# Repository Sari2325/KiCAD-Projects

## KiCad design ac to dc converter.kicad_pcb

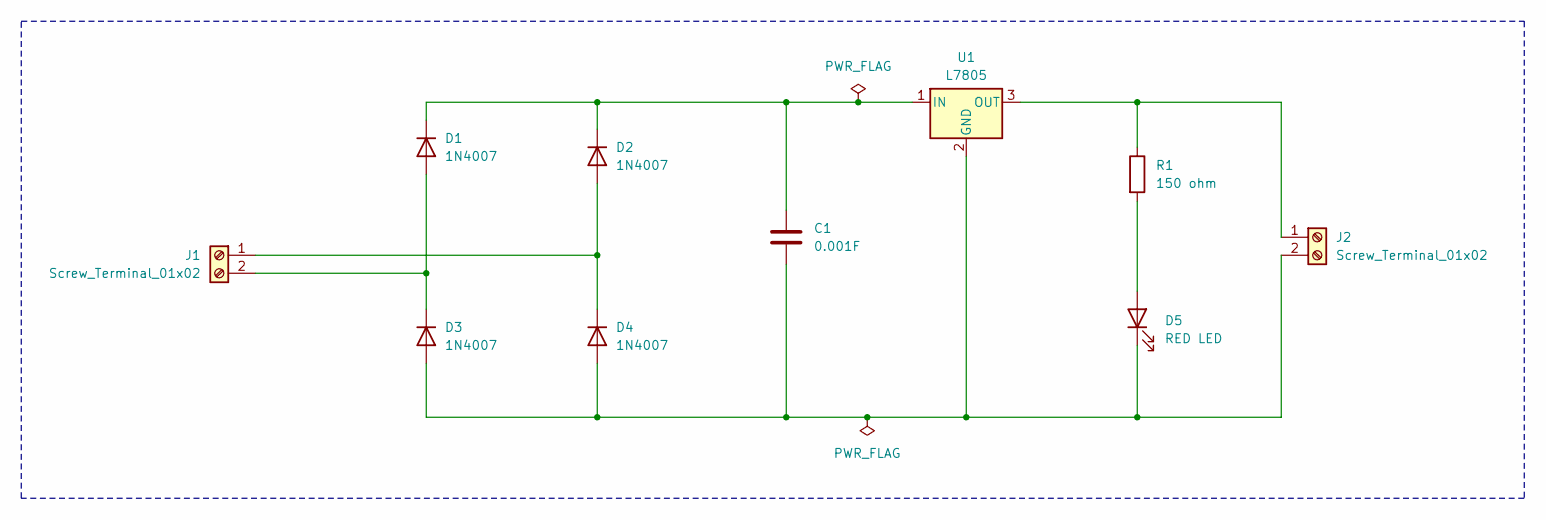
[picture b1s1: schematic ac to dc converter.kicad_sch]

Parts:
C1: 0.001F; C_Radial_D10.0mm_H16.0mm_P5.00mm
D1, D2, D3, D4: 1N4007; D_DO-41_SOD81_P10.16mm_Horizontal
D5: RED LED; LED_D5.0mm
J1, J2: Screw_Terminal_01x02; TerminalBlock_Phoenix_MKDS-3-2-5.08_1x02_P5.08mm_Horizontal
R1: 150 ohm; R_Axial_DIN0207_L6.3mm_D2.5mm_P15.24mm_Horizontal
U1: L7805; TO-220-3_Vertical

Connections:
unnamed: D1.2 (A), D3.1 (K), J1.2
unnamed: C1.1, D1.1 (K), D2.1 (K), U1.1 (IN)
unnamed: D2.2 (A), D4.1 (K), J1.1
unnamed: C1.2, D3.2 (A), D4.2 (A), D5.1 (K), J2.2, U1.2 (GND)
unnamed: D5.2 (A), R1.2
unnamed: J2.1, R1.1, U1.3 (OUT)

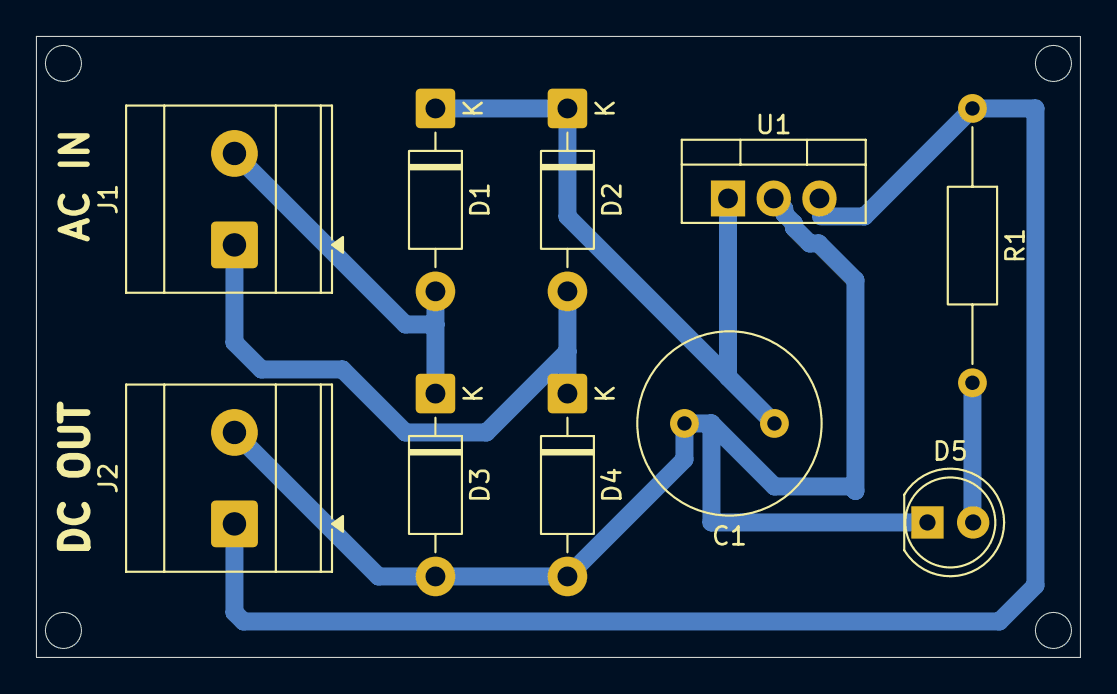
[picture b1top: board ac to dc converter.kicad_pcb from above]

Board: 2 copper layers, 58.0 x 34.5 mm, 10 parts (0 on the bottom side), 6 nets.

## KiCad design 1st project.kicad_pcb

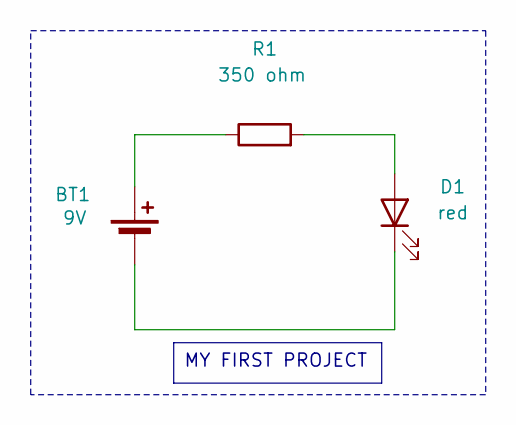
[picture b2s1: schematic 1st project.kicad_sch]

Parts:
BT1: 9V; PinHeader_2x01_P1.00mm_Vertical
D1: red; LED_D5.0mm
R1: 350 ohm; R_Axial_DIN0207_L6.3mm_D2.5mm_P15.24mm_Horizontal

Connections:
unnamed: BT1.1 (+), R1.1
unnamed: BT1.2 (-), D1.1 (K)
unnamed: D1.2 (A), R1.2

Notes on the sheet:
MY FIRST PROJECT

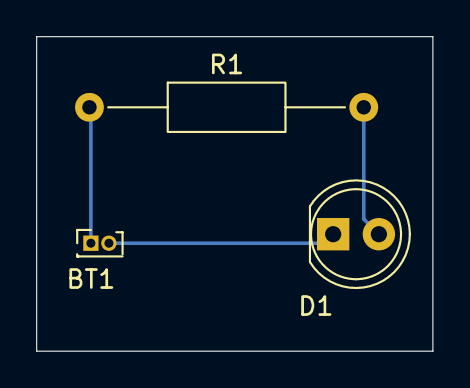
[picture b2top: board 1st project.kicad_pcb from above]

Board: 2 copper layers, 22.0 x 17.5 mm, 3 parts (0 on the bottom side), 3 nets.

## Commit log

2026-06-17 Simple circuit
2026-06-17 5v regulated power supply
    Convert the 230V AC input into 5V DC output
2026-06-17 5V regulated power supply
